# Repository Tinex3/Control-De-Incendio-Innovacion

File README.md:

```bash
git clone --recurse-submodules -j8 git@github.com:Tinex3/Control-De-Incendio-Innovacion.git
```

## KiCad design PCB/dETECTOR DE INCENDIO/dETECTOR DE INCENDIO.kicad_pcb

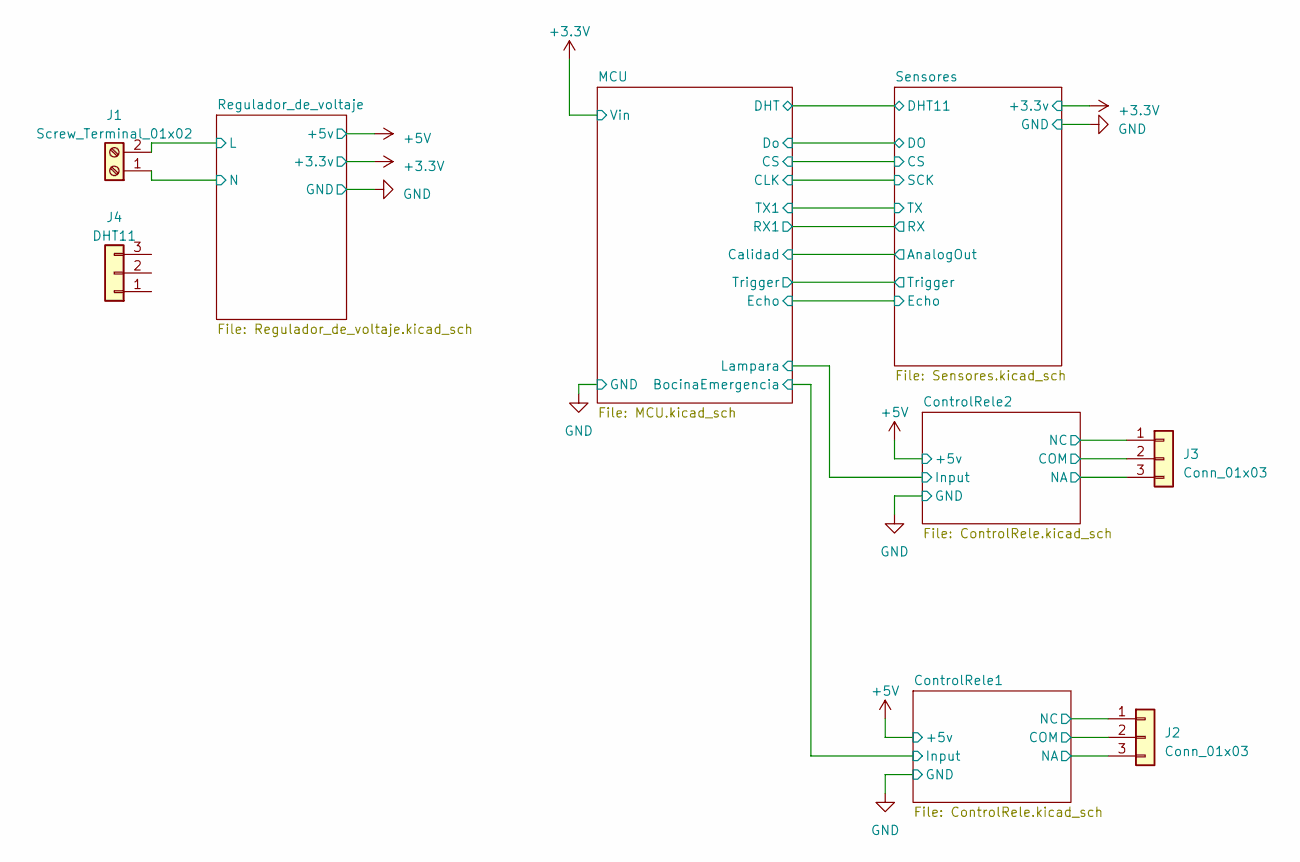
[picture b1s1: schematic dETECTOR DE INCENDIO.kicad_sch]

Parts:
J1: Screw_Terminal_01x02; TerminalBlock_Philmore_TB132_1x02_P5.00mm_Horizontal
J2, J3: Conn_01x03; Molex_KK-396_5273-03A_1x03_P3.96mm_Vertical
J4: DHT11; JST_XH_B3B-XH-A_1x03_P2.50mm_Vertical

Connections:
/ControlRele1/COM: J2.2; also elsewhere on the board
/ControlRele1/NA: J2.3; also elsewhere on the board
/ControlRele1/NC: J2.1; also elsewhere on the board
/ControlRele2/COM: J3.2; also elsewhere on the board
/ControlRele2/NA: J3.3; also elsewhere on the board
/ControlRele2/NC: J3.1; also elsewhere on the board
/Regulador_de_voltaje/L: J1.2; also elsewhere on the board
/Regulador_de_voltaje/N: J1.1; also elsewhere on the board

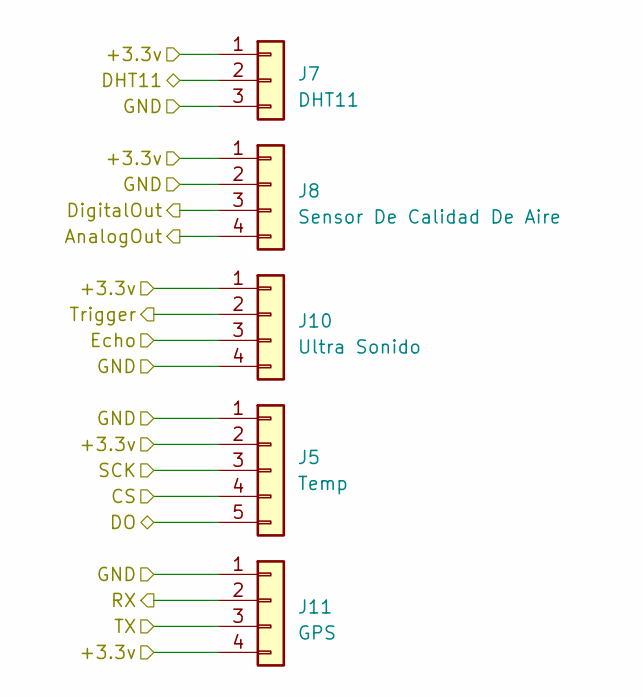
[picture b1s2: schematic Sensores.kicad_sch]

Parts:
J5: Temp; JST_XH_B5B-XH-A_1x05_P2.50mm_Vertical
J7: DHT11; JST_XH_B3B-XH-A_1x03_P2.50mm_Vertical
J8: Sensor De Calidad De Aire; JST_XH_B4B-XH-A_1x04_P2.50mm_Vertical
J10: Ultra Sonido; JST_XH_B4B-XH-A_1x04_P2.50mm_Vertical
J11: GPS; JST_XH_B4B-XH-A_1x04_P2.50mm_Vertical

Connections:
+3.3V: J5.2, J7.1, J8.1, J10.1, J11.4; also elsewhere on the board
/MCU/CLK: J5.3; also elsewhere on the board
/MCU/CS: J5.4; also elsewhere on the board
/MCU/Calidad: J8.4; also elsewhere on the board
/MCU/DHT: J7.2; also elsewhere on the board
/MCU/Do: J5.5; also elsewhere on the board
/MCU/Echo: J10.3; also elsewhere on the board
/MCU/RX1: J11.2; also elsewhere on the board
/MCU/TX1: J11.3; also elsewhere on the board
/MCU/Trigger: J10.2; also elsewhere on the board
/Sensores/DigitalOut: J8.3
GND: J5.1, J7.3, J8.2, J10.4, J11.1; also elsewhere on the board

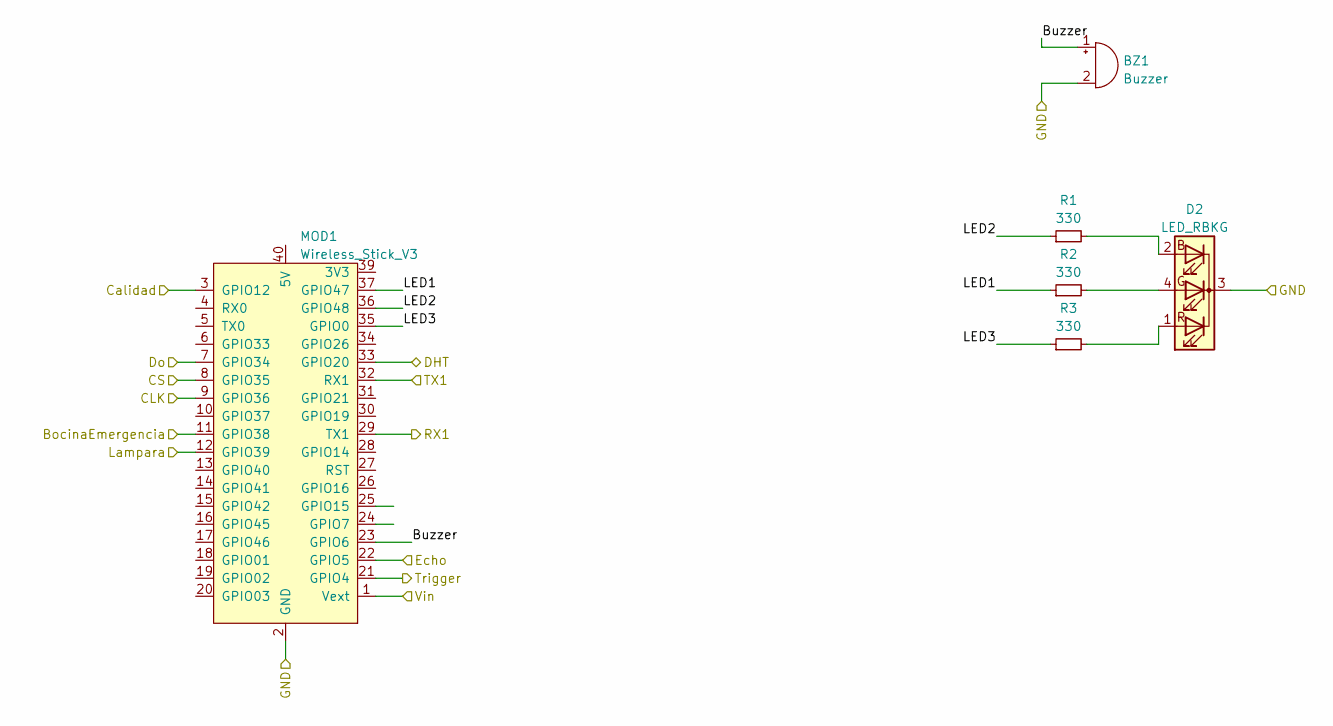
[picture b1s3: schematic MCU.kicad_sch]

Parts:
BZ1: Buzzer; Buzzer_12x9.5RM7.6
D2: LED_RBKG; LED_D5.0mm-4_RGB
MOD1: Wireless_Stick_V3; Wireless_Stick_Lite_V3
R1, R2, R3: 330; R_1206_3216Metric

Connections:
+3.3V: MOD1.1 (Vext); also elsewhere on the board
/ControlRele1/Input: MOD1.11 (GPIO38); also elsewhere on the board
/ControlRele2/Input: MOD1.12 (GPIO39); also elsewhere on the board
/MCU/Buzzer: BZ1.1 (-), MOD1.23 (GPIO6)
/MCU/CLK: MOD1.9 (GPIO36); also elsewhere on the board
/MCU/CS: MOD1.8 (GPIO35); also elsewhere on the board
/MCU/Calidad: MOD1.3 (GPIO12); also elsewhere on the board
/MCU/DHT: MOD1.33 (GPIO20); also elsewhere on the board
/MCU/Do: MOD1.7 (GPIO34); also elsewhere on the board
/MCU/Echo: MOD1.22 (GPIO5); also elsewhere on the board
/MCU/LED1: MOD1.37 (GPIO47), R2.1
/MCU/LED2: MOD1.36 (GPIO48), R1.1
/MCU/LED3: MOD1.35 (GPIO0), R3.1
/MCU/RX1: MOD1.29 (TX1); also elsewhere on the board
/MCU/TX1: MOD1.32 (RX1); also elsewhere on the board
/MCU/Trigger: MOD1.21 (GPIO4); also elsewhere on the board
GND: BZ1.2 (+), D2.3 (K), MOD1.2 (GND), MOD1.38 (GND); also elsewhere on the board
unnamed: D2.2 (BA), R1.2
unnamed: D2.4 (GA), R2.2
unnamed: D2.1 (RA), R3.2

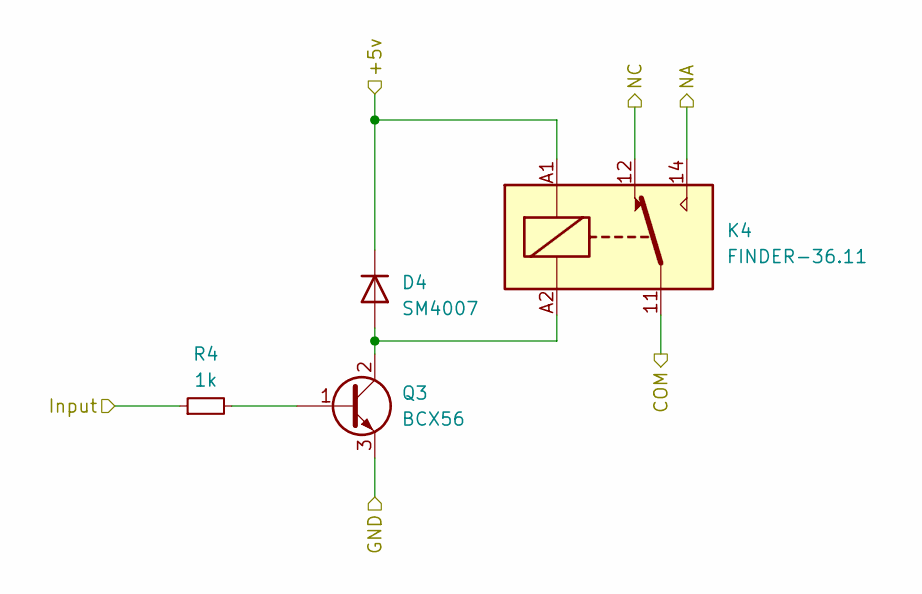
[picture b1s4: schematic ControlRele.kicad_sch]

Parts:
D4: SM4007; D_MELF
K4: FINDER-36.11; Relay_SPDT_Finder_36.11
Q3: BCX56; SOT-89-3
R4: 1k; R_1206_3216Metric

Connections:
+5V: D4.1 (K), K4.A1; also elsewhere on the board
/ControlRele1/Input: R4.1; also elsewhere on the board
/ControlRele2/COM: K4.11; also elsewhere on the board
/ControlRele2/NA: K4.14; also elsewhere on the board
/ControlRele2/NC: K4.12; also elsewhere on the board
GND: Q3.3 (E); also elsewhere on the board
unnamed: Q3.1 (B), R4.2

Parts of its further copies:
D5: SM4007; D_MELF
K3: FINDER-36.11; Relay_SPDT_Finder_36.11
Q4: BCX56; SOT-89-3
R5: 1k; R_1206_3216Metric

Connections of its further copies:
+5V: D5.1 (K), K3.A1; also elsewhere on the board
/ControlRele1/COM: K3.11; also elsewhere on the board
/ControlRele1/NA: K3.14; also elsewhere on the board
/ControlRele1/NC: K3.12; also elsewhere on the board
/ControlRele2/Input: R5.1; also elsewhere on the board
GND: Q4.3 (E); also elsewhere on the board
unnamed: Q4.1 (B), R5.2

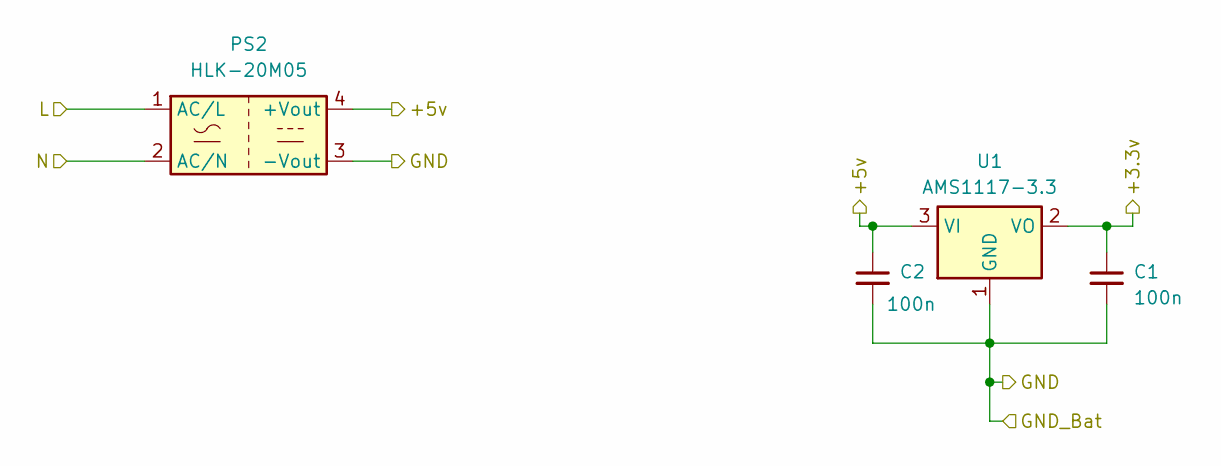
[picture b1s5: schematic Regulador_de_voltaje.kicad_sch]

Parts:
C1, C2: 100n; C_1206_3216Metric
PS2: HLK-20M05; Converter_ACDC_Hi-Link_HLK-20Mxx
U1: AMS1117-3.3; SOT-223-3_TabPin2

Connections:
+3.3V: C1.1, U1.2 (VO); also elsewhere on the board
+5V: C2.1, PS2.4 (+Vout), U1.3 (VI); also elsewhere on the board
/Regulador_de_voltaje/L: PS2.1 (AC/L); also elsewhere on the board
/Regulador_de_voltaje/N: PS2.2 (AC/N); also elsewhere on the board
GND: C1.2, C2.2, PS2.3 (-Vout), U1.1 (GND); also elsewhere on the board

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
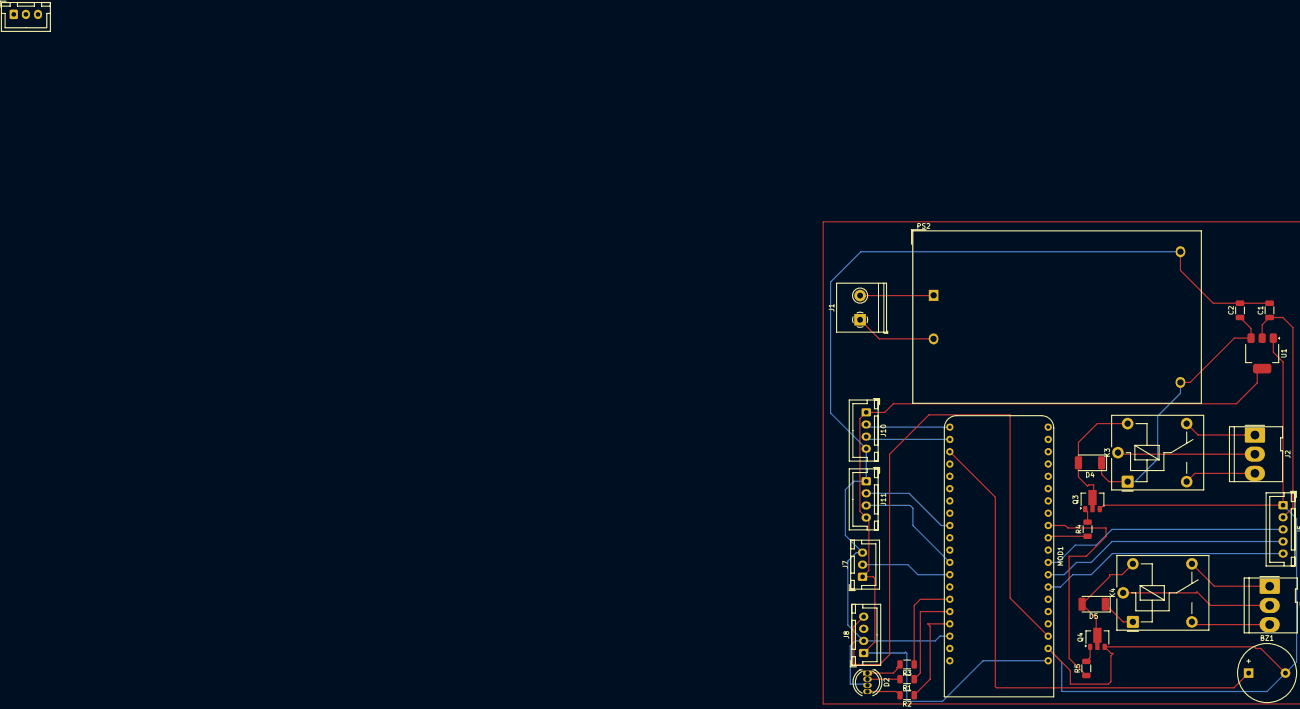
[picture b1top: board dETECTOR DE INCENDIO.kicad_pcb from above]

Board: 2 copper layers, 27 parts (0 on the bottom side), 33 nets.

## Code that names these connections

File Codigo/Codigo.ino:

#include <DHT.h>



#include <max6675.h>
/* 
  Sketch generated by the Arduino IoT Cloud Thing "Untitled 5"
  https://create.arduino.cc/cloud/things/f808a87c-fe38-4ea7-b445-a4675f4c27a1 

  Arduino IoT Cloud Variables description

  The following variables are automatically generated and updated when changes are made to the Thing

  float calidad;
  float humedad;
  float temp;
  float temp2;
  int longitud;

  Variables which are marked as READ/WRITE in the Cloud Thing will also have functions
  which are called when their values are changed from the Dashboard.
  These functions are generated with the Thing and added at the end of this sketch.
*/
#define Sensor 1
#include "thingProperties.h"
#define DHTPIN 16
#define DHTTYPE DHT11
DHT dht(DHTPIN, DHTTYPE);

int thermoDO = 33;
int thermoCS = 34;
int thermoCLK = 36;
MAX6675 thermocouple(thermoCLK, thermoCS, thermoDO);
 const int Trigger = 5;   //Pin digital 2 para el Trigger del sensor
const int Echo = 4;   //Pin digital 3 para el Echo del sensor 
const int pinBuzzer = hs6;
int frecuencia = 2000;
int duracion = 100;

void Task1(void *pvParameters);
void Task2(void *pvParameters);

typedef struct{
  float Longu;
  float temperatura;
}ValueQueue;
ValueQueue value;
QueueHandle_t queue;
SemaphoreHandle_t xSemaphore;

// FunciÃ³n para delay en microsegundos usando FreeRTOS
void delayMicrosecondsRTOS(uint32_t us) {
  const uint32_t tickCount = (us + portTICK_PERIOD_MS * 1000 - 1) / (portTICK_PERIOD_MS * 1000);
  if (tickCount > 0) {
    vTaskDelay(tickCount);
  } else {
    ets_delay_us(us);  // Usar la funciÃ³n del SDK de ESP-IDF para retardos cortos
  }
}


void setup() {
  Serial.begin(9600);
  dht.begin();
  pinMode(Trigger, OUTPUT);
  pinMode(Echo, INPUT);
  digitalWrite(Trigger, LOW);
  delay(1500);
  tone(pinBuzzer, frecuencia, duracion);

  initProperties();
  ArduinoCloud.begin(ArduinoIoTPreferredConnection);
  setDebugMessageLevel(2);
  ArduinoCloud.printDebugInfo();

  queue = xQueueCreate(10, sizeof(ValueQueue));
  xSemaphore = xSemaphoreCreateBinary();

  xTaskCreatePinnedToCore(Task1, "Task1", 10000, NULL, 1, NULL, 0);
  xTaskCreatePinnedToCore(Task2, "Task2", 10000, NULL, 1, NULL, 1);
}

void loop() {
  
  
  
}

void Task1(void *pvParameters) {
  while (true) {
    long t;
    long d;
    digitalWrite(Trigger, HIGH);
    delayMicrosecondsRTOS(10);
    digitalWrite(Trigger, LOW);
    t = pulseIn(Echo, HIGH);
    d = t / 59;
    if (d > 100) d = 0;
    longitud = d;
    float analog = analogRead(Sensor);
    temp2 = thermocouple.readCelsius();
    temp = dht.readTemperature();
    humedad = dht.readHumidity();
    calidad = (analog / 4096) * 100;
    ArduinoCloud.update();
    
    ValueQueue value;
    value.Longu = longitud;
    value.temperatura = temp;
  
    if (xQueueSend(queue, &value, portMAX_DELAY) == pdPASS) {
      xSemaphoreGive(xSemaphore);
    }
    
    vTaskDelay(1000 / portTICK_PERIOD_MS);
  }
}

// ImplementaciÃ³n de la tarea 2
void Task2(void *pvParameters) {
  ValueQueue value;
  while (true) {
    if (xSemaphoreTake(xSemaphore, portMAX_DELAY) == pdTRUE) {
      if (xQueueReceive(queue, &value, portMAX_DELAY) == pdTRUE) {
        Serial.println("Task2 is running on core " + String(xPortGetCoreID()));
        Serial.println("Received Longu: " + String(value.Longu));
        Serial.println("Received Temperature: " + String(value.temperatura));
      }
    }
    vTaskDelay(2000 / portTICK_PERIOD_MS);
  }
}








/*
  Since Longitud is READ_WRITE variable, onLongitudChange() is
  executed every time a new value is received from IoT Cloud.
*/
void onLongitudChange()  {
  // Add your code here to act upon Longitud change
}

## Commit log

2024-05-18 Primer Commit
2024-05-27 se comienza diseno de pcb
2024-05-28 Se crea dise;o preliminar de PCB
